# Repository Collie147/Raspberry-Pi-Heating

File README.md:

# Raspberry-Pi-Heating
<h3>Initial Beta Version</h3>
This is a project to create a customised home heating control on an oil fired heating system.  <br />
The main controller is a Raspberry pi running a python script that controls a 5v Relay module<br />
An SPI touchscreen provides the interface to control the system.<br />
Nginx has been set up on the Raspberry pi also to allow control over web interface.

The Raspberry pi also communicates with an ESP8266-12E to control two valves in a two storey house - upstairs and downstairs.
The valves themselves are turned by stepper motors controlled by an arduino mini.  The ESP8266 pulls pins high to indicate with valve is open. The arduino mini pulls pins high to let the ESP8266 know that the vales are now open and saves it to eeprom in case of power failure.

<i>Valve controller is optional.</i>

<h3>To setup Raspberry Pi:</h3>
Set up Raspberry pi with Raspbian Jessue as per instructions for your touchscreen.<br />
Copy RPiHeatingInstall.zip to /home/pi <br />

<code>sudo raspi-config</code><br />
Advanced --> Select A3 Memory Split --> 16<br />
Advanced --> Select A5 Device Tree --> Yes<br />
Finish<br />
<code>sudo bash /home/pi/RPiHeatingInstall/setup.sh</code><br />
Follow instructions.

Take note of your pinout for your touchscreen as the default settings may conflict with that of your touchscreen.<br />
Make changes as necessary<br />
Assemble parts according to your pinout selected.<br />

<h3>To setup valve controller:</h3>
Set up parts as shown in schematic.<br />
Modify arduino sketches to match your wifi SSID and password<br />
Upload code using Arduino IDE to ESP8266 and Arduino mini

<i>Next version should contain oil tank level meter already in Raspberry pi python script</i>

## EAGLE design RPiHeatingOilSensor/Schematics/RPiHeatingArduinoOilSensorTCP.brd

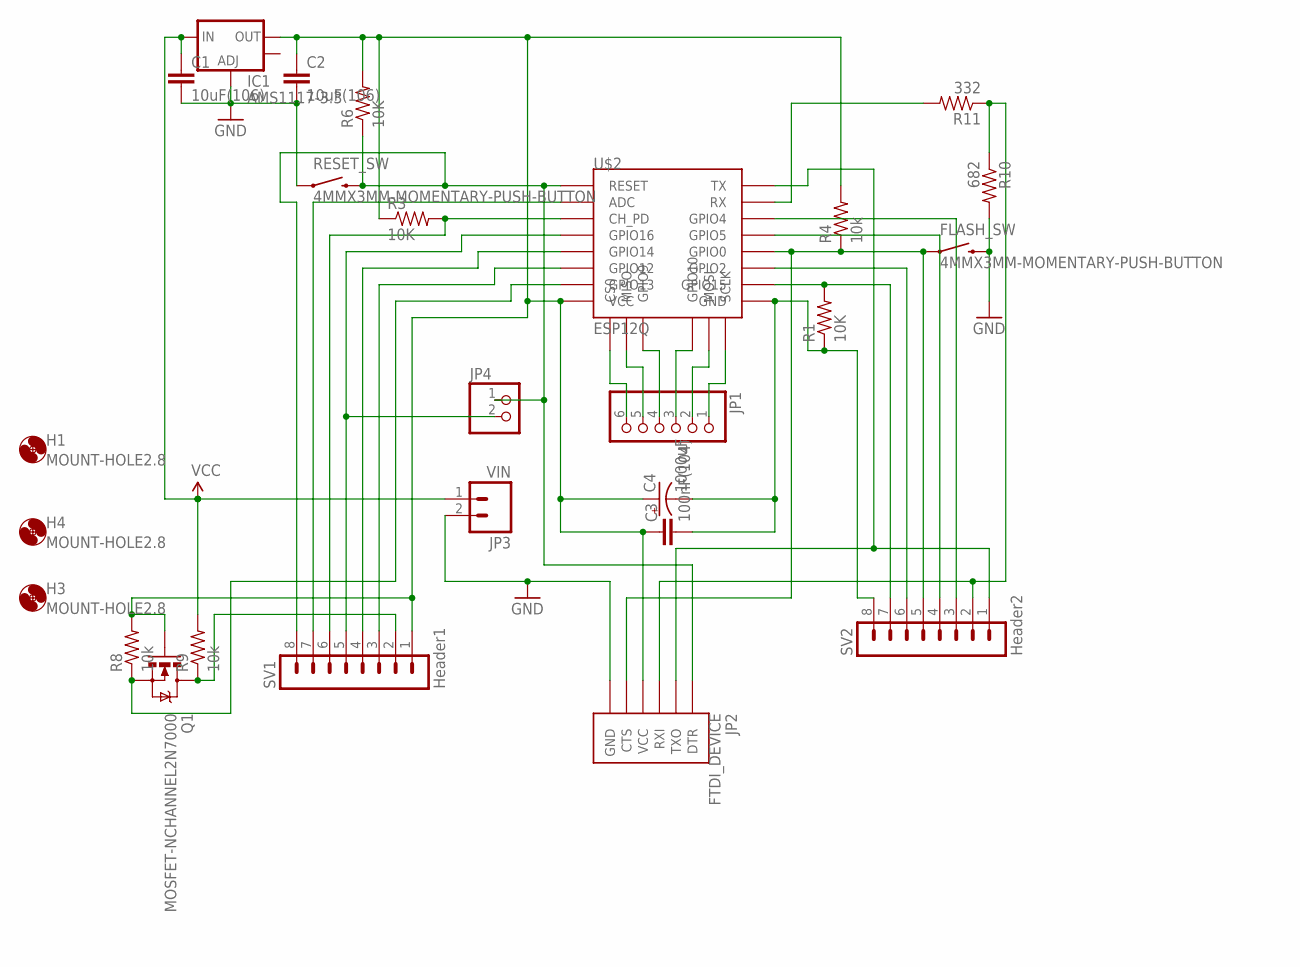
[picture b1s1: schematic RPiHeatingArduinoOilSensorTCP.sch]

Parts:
C1, C2: 10uF(106); 0805
C3: 100nF(104); 0805
C4: 1000uF; CPOL-RADIAL-1000UF-25V
FLASH_SW: 4MMX3MM-MOMENTARY-PUSH-BUTTON
H1, H3, H4: MOUNT-HOLE2.8; 2,8
IC1: AMS1117-3.3; SOT223
JP1: PINHD-1X6; 1X06
JP2: FTDI_DEVICE; FTDI_DEVICE_SIDE
JP3: VIN; 1X02_LOCK_LONGPADS
JP4: PINHD-1X2; 1X02
Q1: MOSFET-NCHANNEL2N7000; TO-92
R1, R3, R6: 10K; 0805
R4, R8, R9: 10k; 0805
R10: 682; 0805
R11: 332; 0805
RESET_SW: 4MMX3MM-MOMENTARY-PUSH-BUTTON
SV1: Header1; MA08-1
SV2: Header2; MA08-1
U$2: ESP12Q

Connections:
3.3V: C2.1, C3.1, C4.1 (+), IC1.2 (OUT), JP2.P$4 (VCC), Q1.2 (G), R3.1, R4.2, R6.2, R8.2, SV1.1, U$2.VCC
5V: C1.1, IC1.3 (IN), JP3.1, R9.2
ADC: SV1.7, U$2.ADC
CH_PD: R3.2, SV1.6, U$2.CH_PD
GND: C1.2, C2.2, FLASH_SW.P$2 (2), IC1.1 (ADJ), JP2.P$6 (GND), JP3.2, R10.2, RESET_SW.P$1 (1)
GPIO0: FLASH_SW.P$1 (1), JP2.P$5 (CTS), R4.1, SV2.5, U$2.GPIO0
GPIO2: SV2.6, U$2.GPIO2
GPIO4: SV2.3, U$2.GPIO4
GPIO5: SV2.4, U$2.GPIO5
GPIO12: SV1.3, U$2.GPIO12
GPIO13: Q1.1 (S), R8.1, U$2.GPIO13
GPIO14: SV1.4, U$2.GPIO14
GPIO15: R1.2, SV2.7, U$2.GPIO15
GPIO16: JP4.2, SV1.5, U$2.GPIO16
GPIOOUT: Q1.3 (D), R9.1, SV1.2
unnamed: C3.2, C4.2 (-), R1.1, SV2.8, U$2.GND
unnamed: JP1.1, U$2.SCLK
unnamed: JP1.2, U$2.MOSI
unnamed: JP1.3, U$2.GPIO10
unnamed: JP1.4, U$2.GPIO9
unnamed: JP1.5, U$2.MISO
unnamed: JP1.6, U$2.CS0
RST: JP2.P$1 (DTR), JP4.1, R6.1, RESET_SW.P$2 (2), SV1.8, U$2.RESET
RX3.3: R11.2, U$2.RX
RX5: JP2.P$3 (RXI), R10.1, R11.1, SV2.2
TX3.3: JP2.P$2 (TXO), SV2.1, U$2.TX

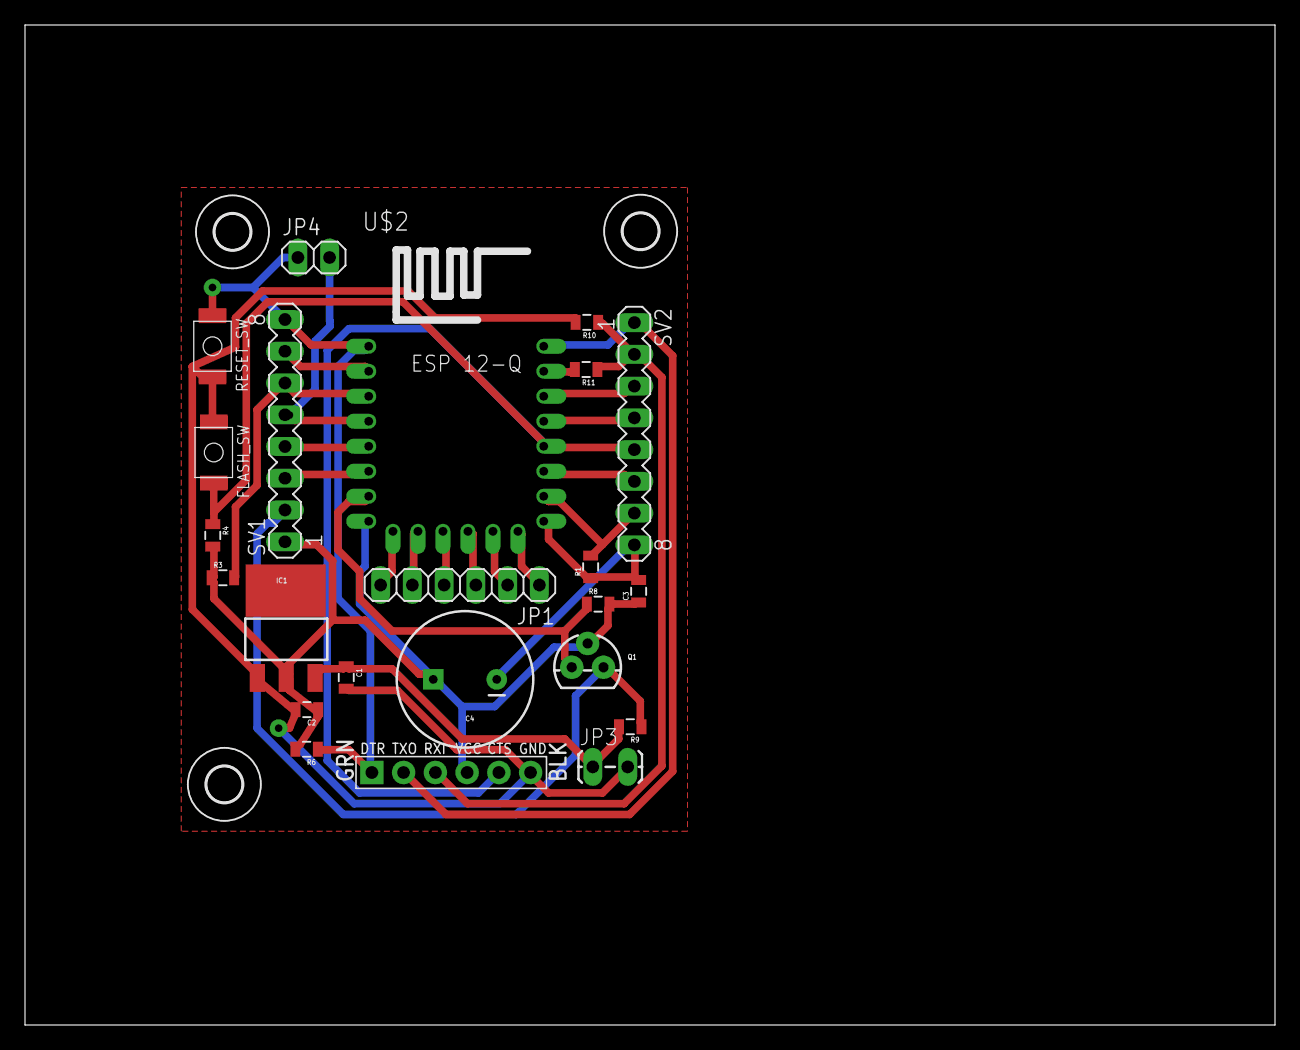
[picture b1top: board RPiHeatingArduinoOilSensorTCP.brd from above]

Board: 2 copper layers, 100.0 x 80.0 mm, 26 parts (0 on the bottom side), 26 nets.

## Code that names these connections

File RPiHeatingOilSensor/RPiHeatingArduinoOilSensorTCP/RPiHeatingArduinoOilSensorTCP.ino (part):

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 *    ESP8266 ESP-07 Pinout
 * RST--------------------TXD
 * ADC--------------------RXD
 * CH_PD----------------GPIO4
 * GPIO16---------------GPIO5
 * GPIO14---------------GPIO0
 * GPIO12---------------GPIO2
 * GPIO13--------------GPIO15
 * VCC--------------------GND
 * 
 * Connections 
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 *  |      |       |
 *  +-4.7K-+       |
 *  |      |       |
 *  3.3v  GPIO5   GND
 *  
 * HC-SR04 
 * VCC----Trig----Echo----GND
 *  |       |      |       |
 *  5v    GPIO4  GPIO13   GND
 *  
 *  ESP8266
 *  GPIO16--> RST (jumper pins)
 *  
 *   Battery --> 100K --> ADC
 *   (>7v)        |
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#include <OneWire.h>
#include <DallasTemperature.h>

#define ONE_WIRE_BUS 5  // DS18B20 pin on GPIO5
OneWire oneWire(ONE_WIRE_BUS);
DallasTemperature DS18B20(&oneWire);

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float tempLong; //float value of the temperature

unsigned int distance; //int value for the distance reading of the HC-SR04
#define TriggerPin 4 //trigger pin on GPIO4
#define EchoPin 13 //echo pin on GPIO 13 - circuit has built in mosfet on GPIO13

//Insert your Tank Dimensions (only for horizontal cylindrical Tank) - calculations are approximate
double Length = 1750; //input the Oil tank dimensions here
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      Serial.println(" Seconds");
    }
  }
  ESP.deepSleep(1000000 * sleepSeconds, RF_NO_CAL); //sleep * seconds(1000000*5=5seconds) - Options (WAKE_RF_DEFAULT, WAKE_RFCAL, WAKE_NO_RFCAL, WAKE_RF_DISABLED) GPIO16 --> RST
}


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
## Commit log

2016-04-05 Initial Beta Version
    First version of code and bash install with schematics. Does not
    include oil tank level meter.
2016-04-05 Initial Beta Version
2016-04-25 Updates and bug fixes
2016-04-25 Bug fix
2016-04-25 Bug Fixes and changes
2016-05-27 Bug Fix and Changes
    Fixed bug in Weather output and added ESP8266 code and schematics for
    Oil Sensor via TCP

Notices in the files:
parts and their libraries:
SparkFun-Passives: Licensing: Creative Commons ShareAlike 4.0 International - https://creativecommons.org/licenses/by-sa/4.0
DECADE-libraries: Licensing: CC v3.0 Share-Alike You are welcome to use this library for commercial purposes.
